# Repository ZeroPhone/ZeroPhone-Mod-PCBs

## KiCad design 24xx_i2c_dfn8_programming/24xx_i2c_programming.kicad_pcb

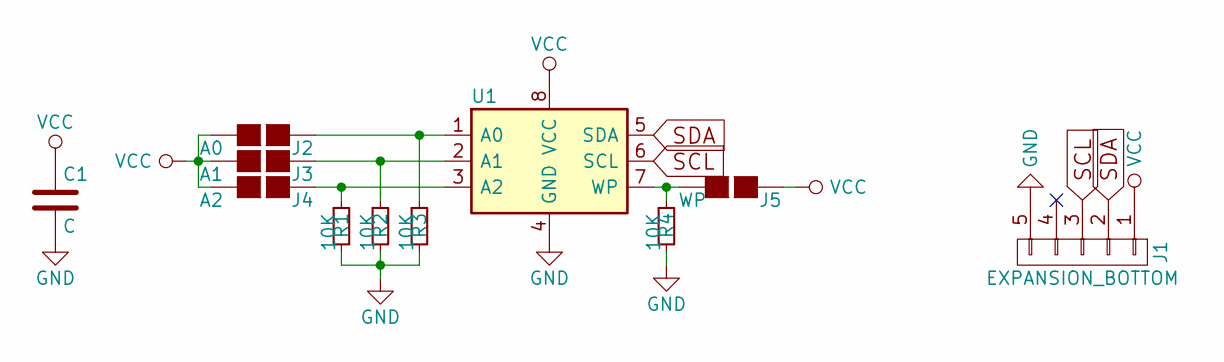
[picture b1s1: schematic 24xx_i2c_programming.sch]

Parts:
C1: C; C_0805_HandSoldering
J1: EXPANSION_BOTTOM; Pin_Header_Straight_1x05_Pitch2.54mm
J2: A0; GS2_SMALL
J3: A1; GS2_SMALL
J4: A2; GS2_SMALL
J5: WP; GS2_SMALL
R1, R2, R3, R4: 10K; R_0805_HandSoldering
U1: 24LC00; DFN-8_3x2mm_Pitch0.5mm

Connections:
GND: C1.2, J1.5, R1.2, R2.2, R3.2, R4.2, U1.4 (GND)
unnamed: J2.1 (G1), R3.1, U1.1 (A0)
unnamed: J3.1 (G1), R2.1, U1.2 (A1)
unnamed: J4.1 (G1), R1.1, U1.3 (A2)
unnamed: J5.2 (G2), R4.1, U1.7 (WP)
SCL: J1.3, U1.6 (SCL)
SDA: J1.2, U1.5 (SDA)
VCC: C1.1, J1.1, J2.2 (G2), J3.2 (G2), J4.2 (G2), J5.1 (G1), U1.8 (VCC)

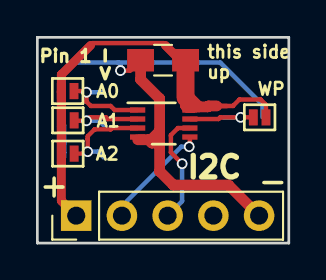
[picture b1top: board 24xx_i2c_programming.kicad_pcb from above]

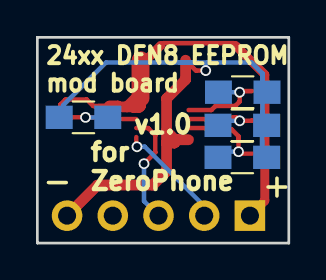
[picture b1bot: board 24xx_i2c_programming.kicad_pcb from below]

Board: 2 copper layers, 14.0 x 11.4 mm, 11 parts (4 on the bottom side), 8 nets.

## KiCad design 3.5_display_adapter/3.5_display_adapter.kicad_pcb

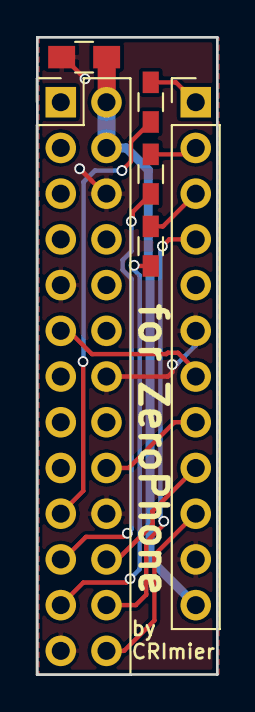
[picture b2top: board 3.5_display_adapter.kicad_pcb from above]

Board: 2 copper layers, 10.0 x 35.4 mm, 6 parts (0 on the bottom side), 13 nets.

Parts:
C1: 100nF; C_0805_HandSoldering
J1: DISPLAY; Pin_Header_Straight_2x13_Pitch2.54mm
J2: SPI_CONN; Pin_Header_Straight_1x12_Pitch2.54mm
R1, R2, R3: 100; R_0603_HandSoldering

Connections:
+5V: C1.1, J1.2, J1.4, J2.12
D_CS: J1.24, J2.4
D_DC: J1.18, J2.8
D_RST: J1.22, J2.9
GND: C1.2, J1.6, J1.9, J1.14, J1.20, J1.25, J2.6, J2.11
MISO: J1.21, R2.2
MOSI: J1.19, R1.2
unnamed: J2.1, R1.1
unnamed: J2.2, R2.1
unnamed: J2.3, R3.1
SCK: J1.23, R3.2
TP_CS: J1.26, J2.10
TP_IRQ: J1.11, J2.7

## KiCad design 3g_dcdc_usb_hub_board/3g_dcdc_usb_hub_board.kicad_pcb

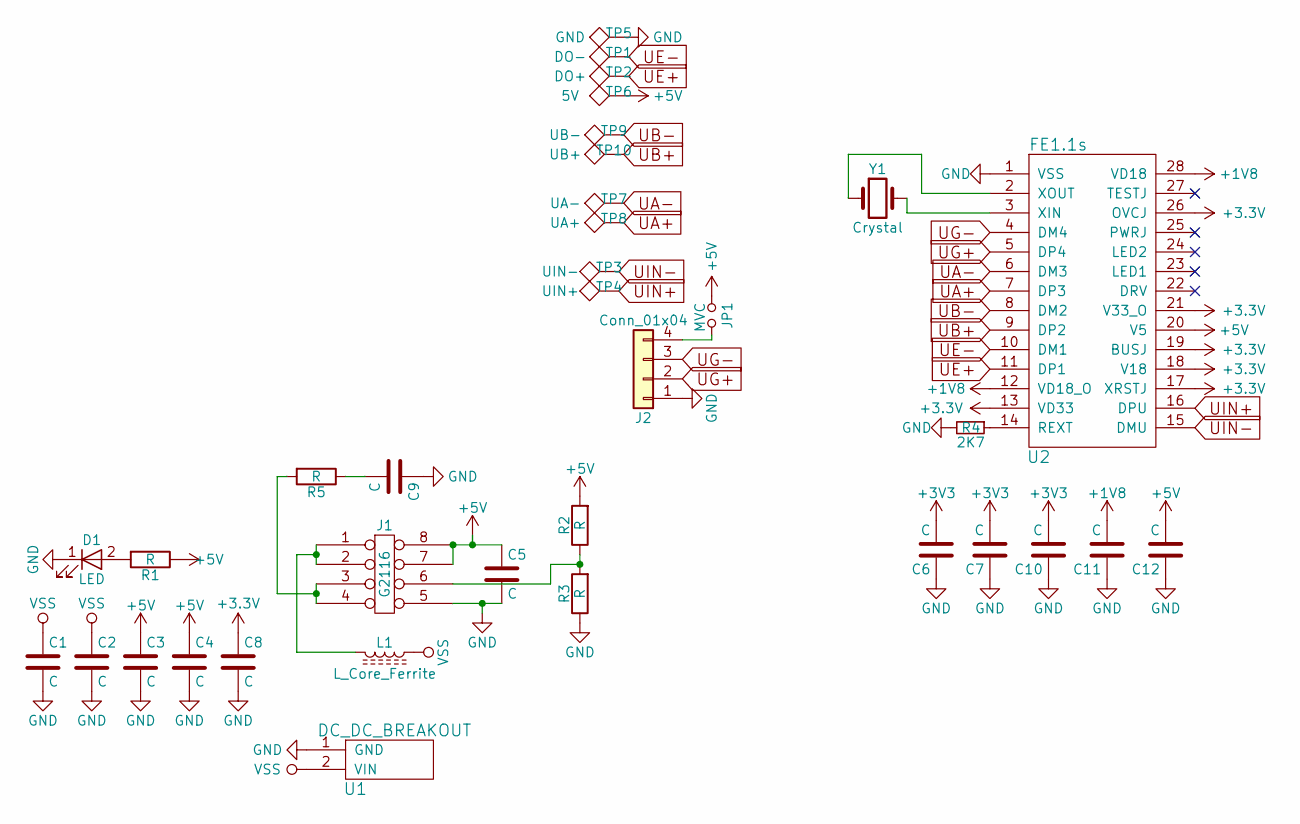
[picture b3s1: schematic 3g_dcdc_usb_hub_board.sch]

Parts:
C1, C3, C6, C7, C8, C9, C10, C11, C12: C; C_0603
C2, C4: C; C_0805
C5: C; C_1206
D1: LED; LED_0603
J1: G2116; SOIC-8-N
J2: Conn_01x04; JST_SH_BM04B-SRSS-TB_04x1.00mm_Straight
JP1: MVC; GS2_SMALL
L1: L_Core_Ferrite; INDUCTOR
R1, R2, R3, R5: R; R_0603
R4: 2K7; R_0603
TP1: DO-; Measurement_Point_Square-TH_Small
TP2: DO+; Measurement_Point_Square-TH_Small
TP3: UIN-; Measurement_Point_Square-SMD-Pad_Small
TP4: UIN+; Measurement_Point_Square-SMD-Pad_Small
TP5: GND; Measurement_Point_Square-TH_Small
TP6: 5V; Measurement_Point_Square-TH_Small
TP7: UA-; Measurement_Point_Round-SMD-Pad_Small
TP8: UA+; Measurement_Point_Round-SMD-Pad_Small
TP9: UB-; Measurement_Point_Round-SMD-Pad_Small
TP10: UB+; Measurement_Point_Round-SMD-Pad_Small
U1: DC_DC_BREAKOUT; DC-DC-BREAKOUT
U2: FE1.1s; SSOP-28_3.9x9.9mm_Pitch0.635mm
Y1: Crystal; Crystal_SMD_3215-2pin_3.2x1.5mm

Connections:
+1V8: C11.2, U2.12 (VD18_O), U2.28 (VD18)
+5V: C3.1, C4.1, C5.1, C12.2, J1.7, J1.8, JP1.1, R1.1, R2.2, TP6.1, U2.20 (V5)
GND: C1.2, C2.2, C3.2, C4.2, C5.2, C6.1, C7.1, C8.2, C9.1, C10.1, C11.1, C12.1, D1.1 (K), J1.5, J2.1, R3.1, R4.2, TP5.1, U1.1 (GND), U2.1 (VSS)
unnamed: C9.2, R5.1
unnamed: D1.2 (A), R1.2
unnamed: J1.1, J1.2, L1.2
unnamed: J1.3, J1.4, R5.2
unnamed: J1.6, R2.1, R3.2
unnamed: J2.4, JP1.2
unnamed: R4.1, U2.14 (REXT)
unnamed: U2.2 (XOUT), Y1.1
unnamed: U2.3 (XIN), Y1.2
UA+: TP8.1, U2.7 (DP3)
UA-: TP7.1, U2.6 (DM3)
UB+: TP10.1, U2.9 (DP2)
UB-: TP9.1, U2.8 (DM2)
UE+: TP2.1, U2.11 (DP1)
UE-: TP1.1, U2.10 (DM1)
UG+: J2.2, U2.5 (DP4)
UG-: J2.3, U2.4 (DM4)
UIN+: TP4.1, U2.16 (DPU)
UIN-: TP3.1, U2.15 (DMU)
VSS: C1.1, C2.1, L1.1, U1.2 (VIN)

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
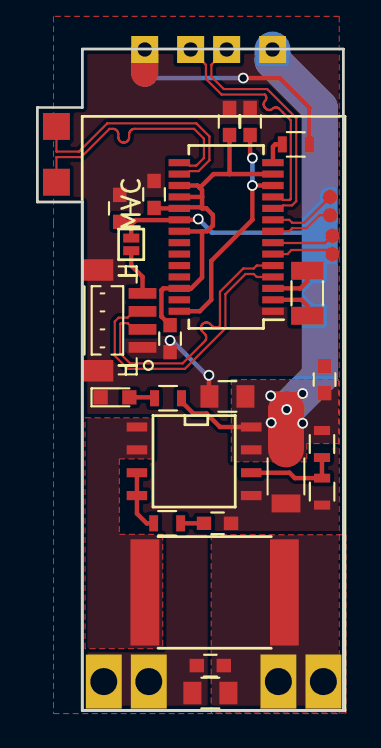
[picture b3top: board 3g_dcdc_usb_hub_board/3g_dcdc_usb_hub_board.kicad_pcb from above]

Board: 2 copper layers, 17.0 x 36.8 mm, 34 parts (0 on the bottom side), 24 nets.

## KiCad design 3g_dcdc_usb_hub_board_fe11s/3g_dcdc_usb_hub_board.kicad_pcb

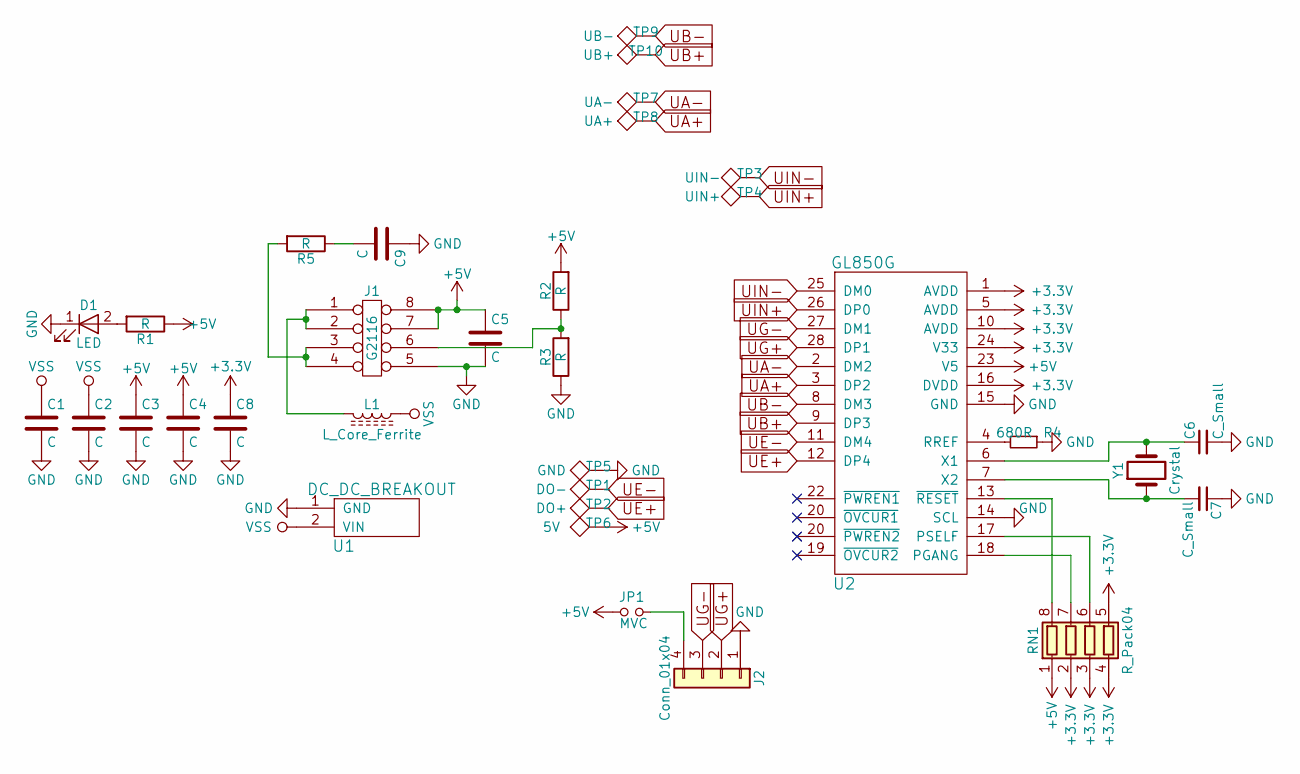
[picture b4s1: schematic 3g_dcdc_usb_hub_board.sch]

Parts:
C1, C3, C8, C9: C; C_0603
C2, C4: C; C_0805
C5: C; C_1206
C6, C7: C_Small; C_0603
D1: LED; LED_0603
J1: G2116; SOIC-8-N
J2: Conn_01x04; JST_SH_BM04B-SRSS-TB_04x1.00mm_Straight
JP1: MVC; GS2_SMALL
L1: L_Core_Ferrite; INDUCTOR
R1, R2, R3, R5: R; R_0603
R4: 680R; R_0603
RN1: R_Pack04; R_Array_Convex_4x0603
TP1: DO-; Measurement_Point_Square-TH_Small
TP2: DO+; Measurement_Point_Square-TH_Small
TP3: UIN-; Measurement_Point_Square-SMD-Pad_Small
TP4: UIN+; Measurement_Point_Square-SMD-Pad_Small
TP5: GND; Measurement_Point_Square-TH_Small
TP6: 5V; Measurement_Point_Square-TH_Small
TP7: UA-; Measurement_Point_Round-SMD-Pad_Small
TP8: UA+; Measurement_Point_Round-SMD-Pad_Small
TP9: UB-; Measurement_Point_Round-SMD-Pad_Small
TP10: UB+; Measurement_Point_Round-SMD-Pad_Small
U1: DC_DC_BREAKOUT; DC-DC-BREAKOUT
U2: GL850G; SSOP-28_3.9x9.9mm_Pitch0.635mm
Y1: Crystal; Crystal_SMD_3215-2pin_3.2x1.5mm

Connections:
+3V3: C8.1, RN1.2 (R2.1), RN1.3 (R3.1), RN1.4 (R4.1), RN1.5 (R4.2), U2.1 (AVDD), U2.5 (AVDD), U2.10 (AVDD), U2.16 (DVDD), U2.24 (V33)
+5V: C3.1, C4.1, C5.1, J1.7, J1.8, JP1.1, R1.1, R2.2, RN1.1 (R1.1), TP6.1, U2.23 (V5)
GND: C1.2, C2.2, C3.2, C4.2, C5.2, C6.2, C7.1, C8.2, C9.1, D1.1 (K), J1.5, J2.1, R3.1, R4.1, TP5.1, U1.1 (GND), U2.14 (SCL), U2.15 (GND)
unnamed: C6.1, U2.6 (X1), Y1.2
unnamed: C7.2, U2.7 (X2), Y1.1
unnamed: C9.2, R5.1
unnamed: D1.2 (A), R1.2
unnamed: J1.1, J1.2, L1.2
unnamed: J1.3, J1.4, R5.2
unnamed: J1.6, R2.1, R3.2
unnamed: J2.4, JP1.2
unnamed: R4.2, U2.4 (RREF)
unnamed: RN1.6 (R3.2), U2.17 (PSELF)
unnamed: RN1.7 (R2.2), U2.18 (PGANG)
unnamed: RN1.8 (R1.2), U2.13 (~RESET)
UA+: TP8.1, U2.3 (DP2)
UA-: TP7.1, U2.2 (DM2)
UB+: TP10.1, U2.9 (DP3)
UB-: TP9.1, U2.8 (DM3)
UE+: TP2.1, U2.12 (DP4)
UE-: TP1.1, U2.11 (DM4)
UG+: J2.2, U2.28 (DP1)
UG-: J2.3, U2.27 (DM1)
UIN+: TP4.1, U2.26 (DP0)
UIN-: TP3.1, U2.25 (DM0)
VSS: C1.1, C2.1, L1.1, U1.2 (VIN)

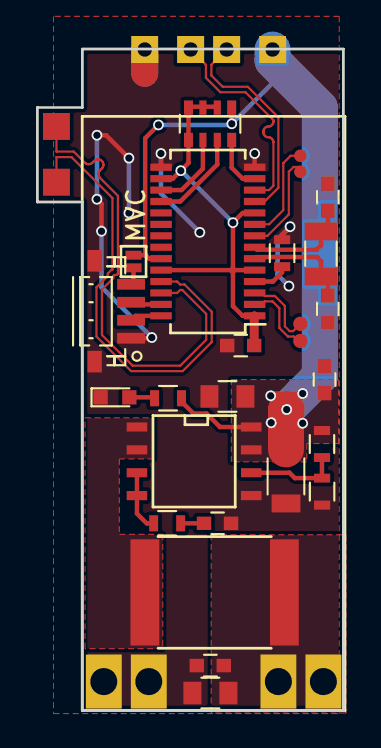
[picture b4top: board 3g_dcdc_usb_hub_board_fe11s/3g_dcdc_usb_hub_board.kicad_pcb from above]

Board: 2 copper layers, 17.0 x 36.8 mm, 33 parts (0 on the bottom side), 26 nets.

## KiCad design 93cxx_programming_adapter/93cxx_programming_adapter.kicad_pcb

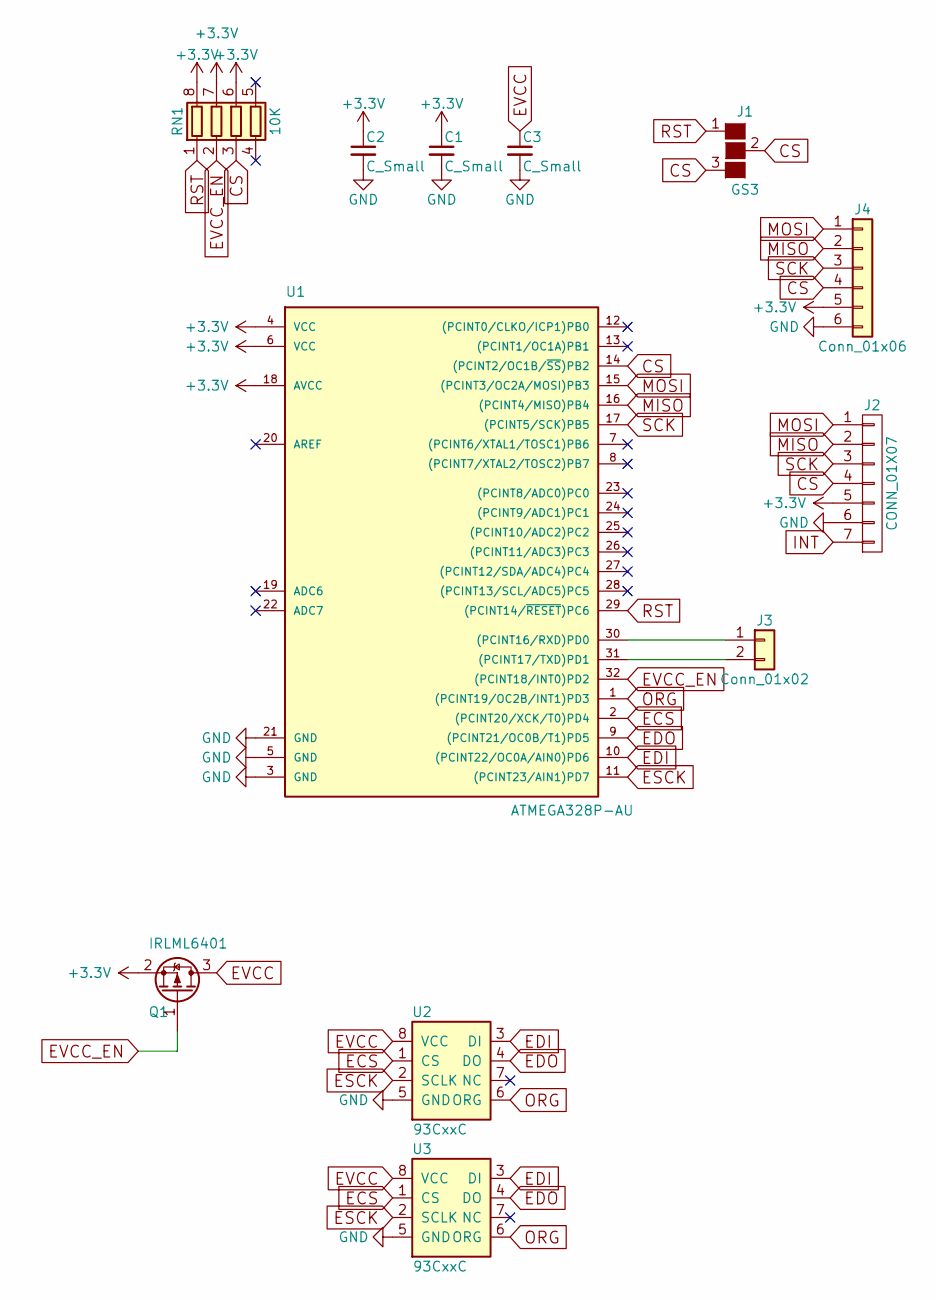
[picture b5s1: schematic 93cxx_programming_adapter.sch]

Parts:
C1, C2, C3: C_Small; C_0805_HandSoldering
J1: GS3
J2: CONN_01X07; Pin_Header_Straight_1x07_Pitch2.54mm
J3: Conn_01x02; Pin_Header_Straight_2x01_Pitch2.00mm
J4: Conn_01x06; Pin_Header_Straight_1x06_Pitch2.54mm
Q1: IRLML6401; SOT-23W_Handsoldering
RN1: 10K; R_Array_Concave_4x0603
U1: ATMEGA328P-AU; QFN-32-1EP_5x5mm_Pitch0.5mm
U2: 93CxxC; SOIC-8_3.9x4.9mm_Pitch1.27mm
U3: 93CxxC; DIP-8_W7.62mm

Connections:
+3V3: C1.1, C2.1, J2.5, J4.5, Q1.2 (S), RN1.6 (R3.2), RN1.7 (R2.2), RN1.8 (R1.2), U1.4 (VCC), U1.6 (VCC), U1.18 (AVCC)
CS: J1.2 (G2), J1.3 (G3), J2.4, J4.4, RN1.3 (R3.1), U1.14 ((PCINT2/OC1B/~SS~)PB2)
ECS: U1.2 ((PCINT20/XCK/T0)PD4), U2.1 (CS), U3.1 (CS)
EDI: U1.10 ((PCINT22/OC0A/AIN0)PD6), U2.3 (DI), U3.3 (DI)
EDO: U1.9 ((PCINT21/OC0B/T1)PD5), U2.4 (DO), U3.4 (DO)
ESCK: U1.11 ((PCINT23/AIN1)PD7), U2.2 (SCLK), U3.2 (SCLK)
EVCC: C3.1, Q1.3 (D), U2.8 (VCC), U3.8 (VCC)
EVCC_EN: Q1.1 (G), RN1.2 (R2.1), U1.32 ((PCINT18/INT0)PD2)
GND: C1.2, C2.2, C3.2, J2.6, J4.6, U1.3 (GND), U1.5 (GND), U1.21 (GND), U1.33, U2.5 (GND), U3.5 (GND)
MISO: J2.2, J4.2, U1.16 ((PCINT4/MISO)PB4)
MOSI: J2.1, J4.1, U1.15 ((PCINT3/OC2A/MOSI)PB3)
unnamed: J3.1, U1.30 ((PCINT16/RXD)PD0)
unnamed: J3.2, U1.31 ((PCINT17/TXD)PD1)
ORG: U1.1 ((PCINT19/OC2B/INT1)PD3), U2.6 (ORG), U3.6 (ORG)
RST: J1.1 (G1), RN1.1 (R1.1), U1.29 ((PCINT14/~RESET~)PC6)
SCK: J2.3, J4.3, U1.17 ((PCINT5/SCK)PB5)

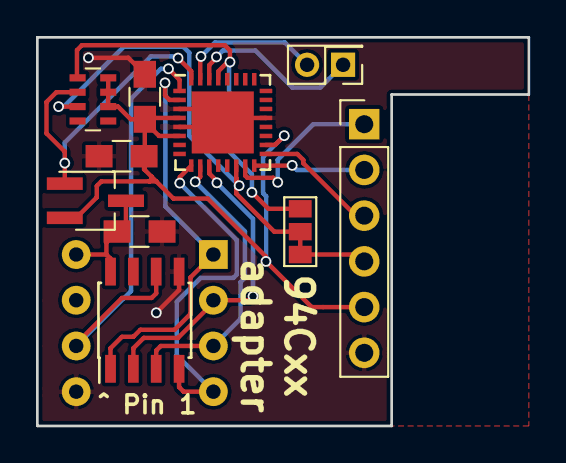
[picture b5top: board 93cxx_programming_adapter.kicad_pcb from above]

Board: 2 copper layers, 27.3 x 21.6 mm, 11 parts (1 on the bottom side), 16 nets.
